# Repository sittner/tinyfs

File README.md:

# TinyFS

TinyFS is a minimalist filesystem designed for extremely constrained embedded systems. The initial reason to create this project was the attempt to build a filesystem that can run on a ZX81 without any additional processors (e.g. an ATMEGA for FAT32 support).

In fact, this was a little bit challenging, because I wanted to use 32k RAM and 32k ROM and due to the architecture of the ZX video system only the lower 16k of ROM is useable for executable code. 8k of that is already used by the original OS, so the code for the FS has to fit into the remaining 8k block. Fortunately the upper 16k is useable to store constant data, so all stuff like that (i.e. strings and initializer data) is stored in that area.

## Quick Start

```c
#include "filesys.h"

int main(void) {
    // Initialize the filesystem
    tfs_init();
    if (tfs_last_error != TFS_ERR_OK) {
        printf("Failed to initialize filesystem\n");
        return 1;
    }
    
    // Write a file
    const char *data = "Hello, TinyFS!";
    tfs_write_file("hello.txt", (uint8_t*)data, strlen(data), 1);
    
    // Read it back
    uint8_t buffer[256];
    uint32_t bytes = tfs_read_file("hello.txt", buffer, sizeof(buffer));
    buffer[bytes] = '\0';
    printf("Read: %s\n", buffer);
    
    return 0;
}
```

See [docs/USAGE_EXAMPLES.md](docs/USAGE_EXAMPLES.md) for more examples.

## Features

TinyFS is designed for extreme simplicity and minimal resource usage, making deliberate trade-offs between features and footprint.

### Capabilities

* **Maximum volume size:** Up to 2TB (terabytes)
* **Maximum file size:** Up to 4GB (gigabytes)
* **Efficient metadata access:** Direct block addressing
* **Low code size:** ~6-15 KB depending on features
* **Low RAM usage:** ~1-3 KB depending on configuration
* **Static memory management:** No dynamic allocation
* **Sequential and random file access:** With Extended API
* **Subdirectory support:** Unlimited nesting depth
* **Portable:** Easy to port to any platform with block storage

### Limitations

To achieve minimal resource usage, the following features are intentionally omitted:

* **No timestamps:** No creation, access, or modification times
* **No file attributes:** No permissions, ownership, or ACLs
* **No caching:** Direct block I/O (simple but slower)
* **No redundancy:** Limited error recovery from corruption
* **Fixed block size:** 512 bytes only (matches SD card sectors)

These trade-offs make TinyFS ideal for extremely constrained systems where FAT32, ext2, or other filesystems won't fit.

## Hardware

The hardware is a ZX81 expansion board consisting of 32kB RAM and ROM as well as
an SD card interface. It was important to me to only use hardware (apart from
the SD card itself) that would also have been available in the era of the ZX81.
That's why I deliberately did not use FPGA, CPLD or coprocessors.

[See the ZXSD schematic](https://github.com/sittner/tinyfs/raw/main/zx81/hardware/zxsd.pdf).

The board contains a memory expansion, because we need some RAM for variables
and buffers and obviously ROM to store the file system code.

The Memory map looks as this:

| Address area    | Mapped device    | Usage                                                          |
|-----------------|------------------|----------------------------------------------------------------|
| 0x0000 - 0x3FFF | ROM (lower 16kB) | 0x0000 - 0x1FFF: Original ROM code (patched with TinyFS hooks) |
|                 |                  | 0x2000 - 0x3FFF: TinyFS code                                   |
| 0x4000 - 0x7FFF | RAM (lower 16kB) | Normal ZX81 RAM (available to the user)                        |
| 0x8000 - 0xBFFF | ROM (upper 16kB) | Constant data for TinyFS                                       |
| 0xC000 - 0xFFFF | RAM (upper 16kB) | 0xC000 - 0xF7FF: Unused (could be used as DFILE e.g. for HRG)  |
|                 |                  | 0xF800 - 0xFFFF: TinyFS variables and buffers                  |

Unfortunately, I've found no easy way to allow RAM in the 0x2000 - 0x3FFF area,
which means that the board will not work with WRX16. The NOP logic of the ZX81
requires that the TinyFS code resides in the lower 32kB area to be executable,
and I've preferred to provide 16kB of RAM.

Other hires systems like WRX1K, Kevin Baker's HIRES16K or HRG-ms seems to work.

Many thanks to Siggi who helped me much in streamlining the memory encoder stuff.

## Supported Platforms

TinyFS has been ported to multiple platforms and can be adapted to any system with block storage.

### Official Ports

* **ZX81** - Z80 with SD card via custom hardware SPI
  - ROM: ~8 KB, RAM: ~1 KB
  - Case-insensitive filenames
  - Sequential access only
  
* **AVR (ATmega328P)** - 8-bit AVR with SD card via hardware SPI
  - Flash: ~10 KB, RAM: ~1 KB
  - Format support
  - Sequential access only
  
* **Linux (FUSE)** - Full-featured desktop implementation
  - File-backed or block device
  - All features enabled
  - Random file access with up to 32 file descriptors

### Custom Platforms

TinyFS can be ported to any platform that provides:
- Block storage with 512-byte sectors (SD/MMC cards, flash, file emulation)
- Approximately 1-3 KB of RAM
- Approximately 6-15 KB of ROM/Flash for code

See [docs/PORTING_GUIDE.md](docs/PORTING_GUIDE.md) for porting instructions.

## Documentation

Comprehensive documentation is available in the `docs/` directory:

* **[ARCHITECTURE.md](docs/ARCHITECTURE.md)** - Filesystem design and internal structures
  - Overview of block types (bitmap, directory, data)
  - Block size and layout details
  - Memory usage and limitations
  
* **[API_REFERENCE.md](docs/API_REFERENCE.md)** - Complete API documentation
  - All public functions with examples
  - Error codes and handling
  - Basic and Extended API reference
  
* **[CONFIGURATION.md](docs/CONFIGURATION.md)** - Configuration options guide
  - Feature flags (format, extended API, etc.)
  - Platform-specific settings
  - Memory vs. features trade-offs
  
* **[USAGE_EXAMPLES.md](docs/USAGE_EXAMPLES.md)** - Practical code examples
  - Basic file operations
  - Directory navigation
  - Random access I/O (Extended API)
  - Error handling patterns
  
* **[PORTING_GUIDE.md](docs/PORTING_GUIDE.md)** - How to port to new platforms
  - Required interface functions
  - Platform examples (AVR, Linux, ZX81)
  - Testing and troubleshooting
  
* **[INTERNAL_DESIGN.md](docs/INTERNAL_DESIGN.md)** - Implementation details
  - Block buffer management
  - Allocation algorithms
  - Seek optimization
  - Performance characteristics

## Ports

### ZX81

All SD card access is done by LOAD and SAVE commands prefixed by a ':' as
file name:

| Command              | Description                                                     |
|----------------------|-----------------------------------------------------------------|
| LOAD ":?"            | show drive info                                                 |
| LOAD ":*"            | show drive info with used blocks (could be very time-consuming) |
| LOAD ":"             | show current dir                                                |
| LOAD ":/"            | change to root dir                                              |
| LOAD ":<"            | change to parent dir                                            |
| LOAD ":>[DIRNAME]"   | change to DIRNAME                                               |
| LOAD ":[FILENAME]"   | load file FILENAME                                              |
| SAVE ":$"            | format disk                                                     |
| SAVE ":>[DIRNAME]"   | create dir DIRNAME                                              |
| SAVE ":=[OLD]:[NEW]" | rename file [OLD] to [NEW]                                      |
| SAVE ":-[FILENAME]"  | delete file [FILENAME]                                          |
| SAVE ":[FILENAME]"   | save file FILENAME                                              |

Without prefix, LOAD/SAVE acts as normal tape operation.

To build the hex file for the ROM you will need [SDCC](https://sdcc.sourceforge.net/)
version [4.5.0](https://sourceforge.net/projects/sdcc/files/sdcc/4.5.0/sdcc-src-4.5.0.tar.bz2/download).

### Linux

To allow easy access to the file system on the SD card from outside the ZX81
world there is a Linux FUSE port as well. This could easily be build via the
included Makefile. As dependency, only libfuse is required.

You can format a SD card, for example:

    sudo ./mktfs /dev/mmcblk0

To mount the SD card, you could use:

    sudo ./tfs -f -o uid=1000,gid=1000,allow_other /dev/mmcblk0 /mnt

Don't forget to umount after work is done:

    sudo umount /mnt

### AVR

This port currently runs on a ATMEGA328P. It provides a simple CLI accessible
via UART @9600 Baud. The main intention of this port was to start developing
the FS code before the actual zx81 hardware was finished, so it is currently
not tested very well.

## Internal structure

Only three types of disk blocks exists:

* Bitmap blocks
* Directory blocks
* Data blocks

### Bitmap blocks

Bitmap blocks are used to track allocated/free blocks. There is stored no meta
data information inside these block, just a plain bit array for 8 x 512 = 4096
bits. If a block is in use, a '1' on the corresponding location is indicating
this.

The bitmap block itself is always marked as used, so the first bit of the bitmap
block is always set to '1'. The following 2023 Blocks can be uses as directory
or data blocks.

Offset calculation is very simple, since the first bitmap block is located on
the beginning of the storage device (block offset 0) and the subsequent bitmap
blocks will be following every 4096 blocks. So the position of the corresponding
bitmap block for a given data/directory block can be calculated by logical
shift/and operations.

The last used bitmap block with free block available is cached in memory to
speed up allocation for data/directory blocks. The bitmap block is needed to read
only once and every following allocation of further blocks just require an write
operation to keep the mapping data on disk up to date. 

### Directory blocks

Directory block are the most complex structures of this file system. They are
used to organize files and subdirectories and store the names of these items.

To allow a virtually unlimited count of items per directory layer and simplify
the process of allocation/freeing directory blocks, they are built as double
linked list. The member *parent* always pointed to the corresponding parent
directory block. A value of '0' is indicating that we are on a root directory
block. The first root directory block on disk could be found on block offset 1.

    typedef struct {
      uint32_t prev;
      uint32_t next;
      uint32_t parent;
      TFS_DIR_ITEM items[];
    } _PACKED TFS_DIR_BLK;

There are 20 items per directory block. An item could be one of the type *free*,
*dir* or *file*. The member *blk* pointed to either the corresponding sub
directory block or to the first data block of the corresponding file. The member
*size* holds the size of the entire file (in case of a subdirectory item it is
set to '0').
    
    #define TFS_NAME_LEN 16

    typedef struct {
      uint32_t blk;
      uint32_t size;
      uint8_t type;
      char name[TFS_NAME_LEN];
    } _PACKED TFS_DIR_ITEM;
    
    #define TFS_DIR_ITEM_FREE 0
    #define TFS_DIR_ITEM_DIR  1
    #define TFS_DIR_ITEM_FILE 2

### Data blocks

These blocks contain the actual file data. They are chained as double linked
list and holding 504 bytes of user data each.

    typedef struct {
      uint32_t prev;
      uint32_t next;
      uint8_t data[];
    } _PACKED TFS_DATA_BLK;

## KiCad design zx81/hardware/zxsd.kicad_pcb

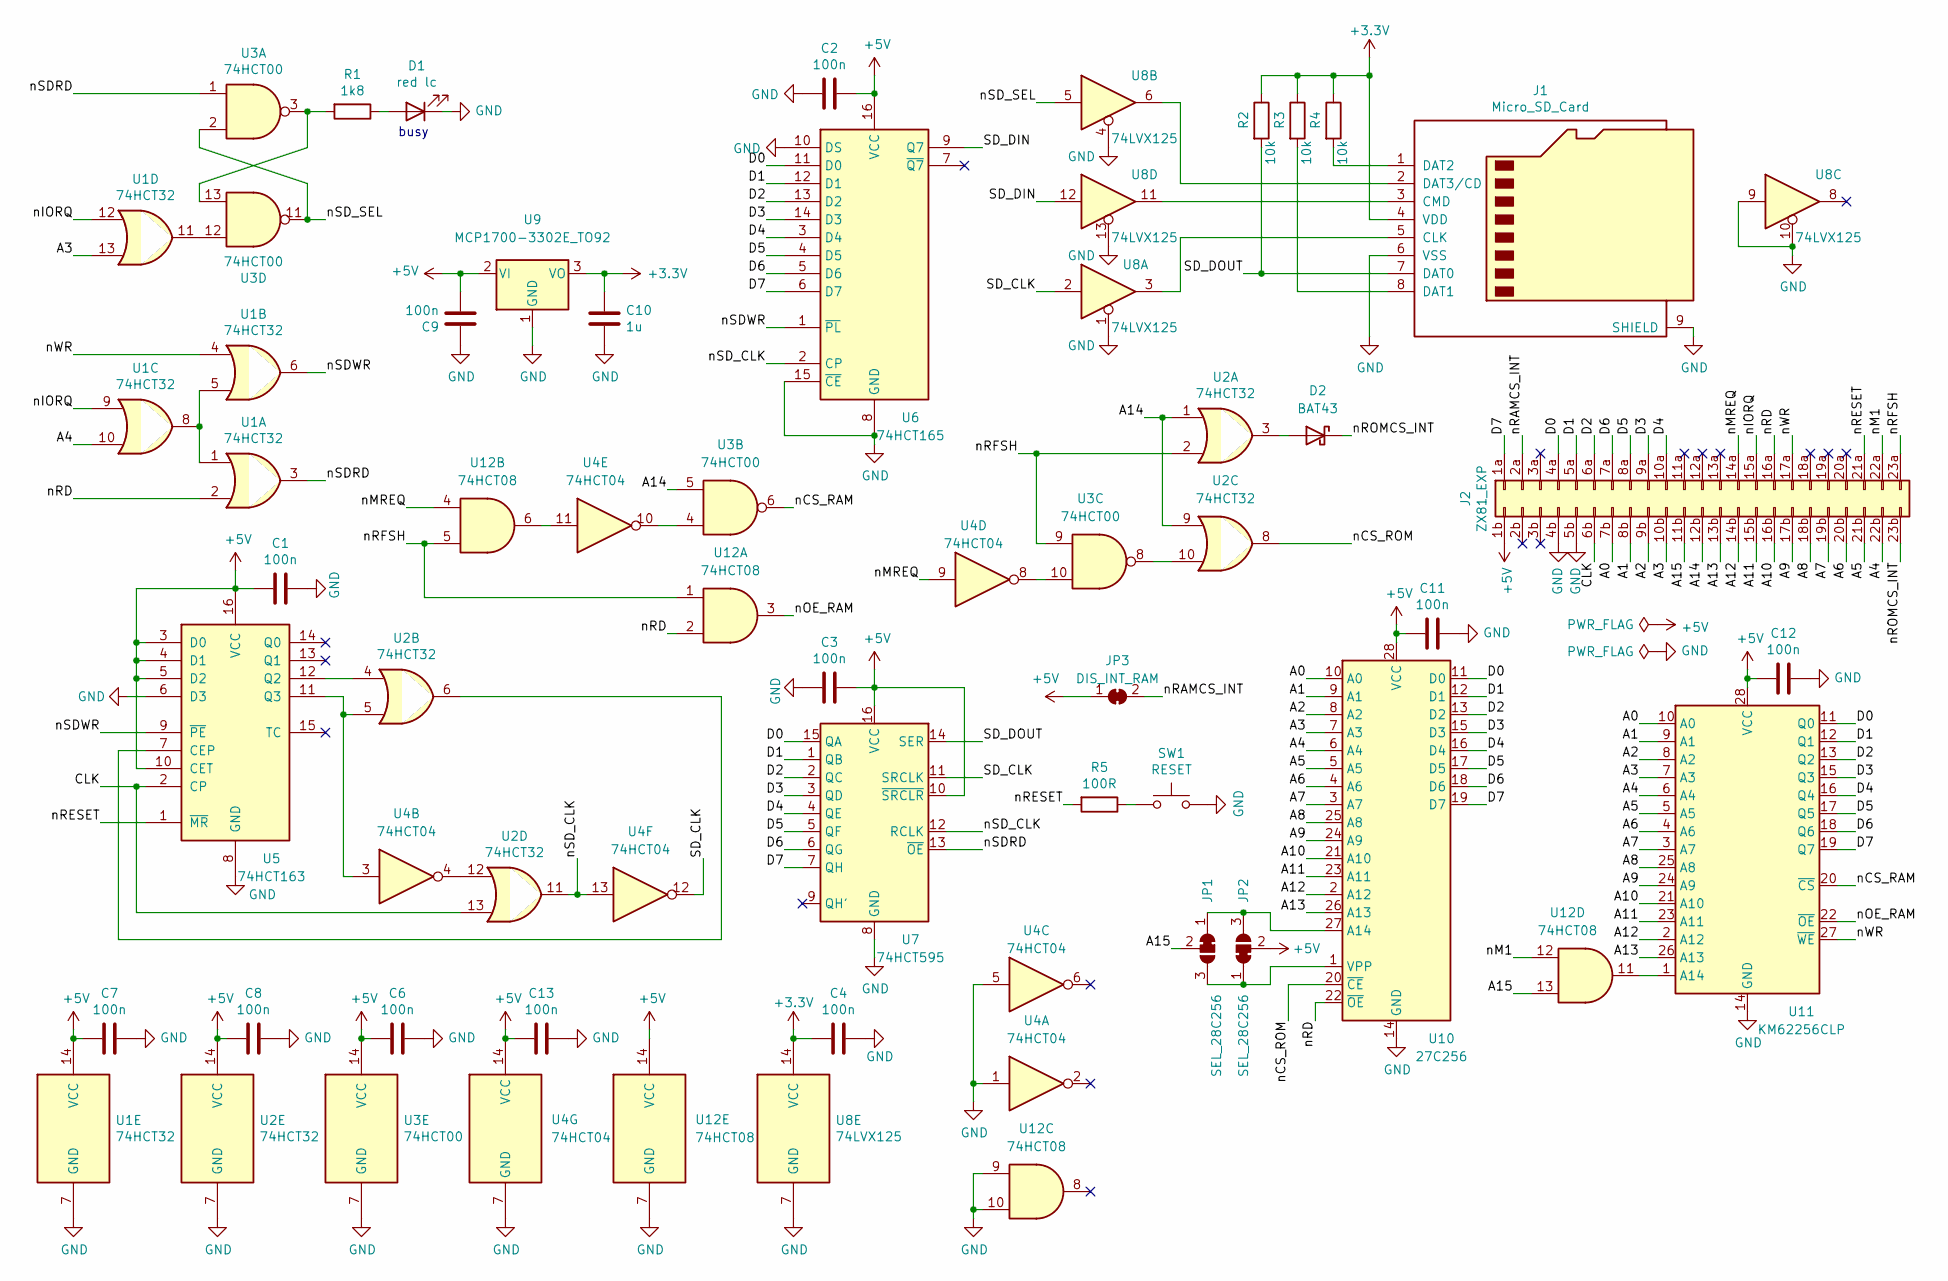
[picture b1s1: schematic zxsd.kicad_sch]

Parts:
C1, C2, C3, C4, C6, C7, C8, C9, C11, C12, C13: 100n; C_Disc_D5.0mm_W2.5mm_P5.00mm
C10: 1u; C_Disc_D5.0mm_W2.5mm_P5.00mm
D1: red lc; LED_D3.0mm
D2: BAT43; D_DO-35_SOD27_P2.54mm_Vertical_AnodeUp
J1: Micro_SD_Card; microSD_HC_Wuerth_693072010801
J2: ZX81_EXP; ZX81_EXP_EXT
JP1, JP2: SEL_28C256; SolderJumper-3_P1.3mm_Bridged12_RoundedPad1.0x1.5mm_NumberL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
JP3: DIS_INT_RAM; SolderJumper-2_P1.3mm_Bridged_RoundedPad1.0x1.5mm
R1: 1k8; R_Axial_DIN0207_L6.3mm_D2.5mm_P10.16mm_Horizontal
R2, R3, R4: 10k; R_Axial_DIN0207_L6.3mm_D2.5mm_P10.16mm_Horizontal
R5: 100R; R_Axial_DIN0207_L6.3mm_D2.5mm_P10.16mm_Horizontal
SW1: RESET; SW_PUSH_6mm
U1, U2: 74HCT32; DIP-14_W7.62mm_Socket_LongPads
U3: 74HCT00; DIP-14_W7.62mm_Socket_LongPads
U4: 74HCT04; DIP-14_W7.62mm_Socket_LongPads
U5: 74HCT163; DIP-16_W7.62mm_Socket_LongPads
U6: 74HCT165; DIP-16_W7.62mm_Socket_LongPads
U7: 74HCT595; DIP-16_W7.62mm_Socket_LongPads
U8: 74LVX125; SO-14_3.9x8.65mm_P1.27mm
U9: MCP1700-3302E_TO92; TO-92_Inline
U10: 27C256; DIP-28_W15.24mm_Socket_LongPads
U11: KM62256CLP; DIP-28_W15.24mm_Socket_LongPads
U12: 74HCT08; DIP-14_W7.62mm_Socket_LongPads

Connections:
+3.3V: C4.2, C10.1, J1.4 (VDD), R2.1, R3.1, R4.1, U8.14 (VCC), U9.3 (VO)
+5V: C1.1, C2.1, C3.1, C6.1, C7.1, C8.1, C9.1, C11.1, C12.1, C13.1, J2.1b, JP2.2 (C), JP3.1 (A), U1.14 (VCC), U2.14 (VCC), U3.14 (VCC), U4.14 (VCC), U5.3 (D0), U5.4 (D1), U5.5 (D2), U5.10 (CET), U5.16 (VCC), U6.16 (VCC), U7.10 (~SRCLR), U7.16 (VCC), U9.2 (VI), U10.28 (VCC), U11.28 (VCC), U12.14 (VCC)
/A0: J2.7b, U10.10 (A0), U11.10 (A0)
/A1: J2.8b, U10.9 (A1), U11.9 (A1)
/A2: J2.9b, U10.8 (A2), U11.8 (A2)
/A3: J2.10b, U1.13, U10.7 (A3), U11.7 (A3)
/A4: J2.22b, U1.10, U10.6 (A4), U11.6 (A4)
/A5: J2.21b, U10.5 (A5), U11.5 (A5)
/A6: J2.20b, U10.4 (A6), U11.4 (A6)
/A7: J2.19b, U10.3 (A7), U11.3 (A7)
/A8: J2.18b, U10.25 (A8), U11.25 (A8)
/A9: J2.17b, U10.24 (A9), U11.24 (A9)
/A10: J2.16b, U10.21 (A10), U11.21 (A10)
/A11: J2.15b, U10.23 (A11), U11.23 (A11)
/A12: J2.14b, U10.2 (A12), U11.2 (A12)
/A13: J2.13b, U10.26 (A13), U11.26 (A13)
/A14: J2.12b, U2.1, U2.9, U3.5
/A15: J2.11b, JP1.2 (C), U12.13
/CLK: J2.6b, U2.13, U5.2 (CP)
/D0: J2.4a, U6.11 (D0), U7.15 (QA), U10.11 (D0), U11.11 (Q0)
/D1: J2.5a, U6.12 (D1), U7.1 (QB), U10.12 (D1), U11.12 (Q1)
/D2: J2.6a, U6.13 (D2), U7.2 (QC), U10.13 (D2), U11.13 (Q2)
/D3: J2.9a, U6.14 (D3), U7.3 (QD), U10.15 (D3), U11.15 (Q3)
/D4: J2.10a, U6.3 (D4), U7.4 (QE), U10.16 (D4), U11.16 (Q4)
/D5: J2.8a, U6.4 (D5), U7.5 (QF), U10.17 (D5), U11.17 (Q5)
/D6: J2.7a, U6.5 (D6), U7.6 (QG), U10.18 (D6), U11.18 (Q6)
/D7: J2.1a, U6.6 (D7), U7.7 (QH), U10.19 (D7), U11.19 (Q7)
/SD_CLK: U4.12, U7.11 (SRCLK), U8.2
/SD_DIN: U6.9 (Q7), U8.12
/SD_DOUT: J1.7 (DAT0), R2.2, U7.14 (SER)
/nCS_RAM: U3.6, U11.20 (~CS)
/nCS_ROM: U2.8, U10.20 (~CE)
/nIORQ: J2.15a, U1.9, U1.12
/nM1: J2.22a, U12.12
/nMREQ: J2.14a, U4.9, U12.4
/nOE_RAM: U11.22 (~OE), U12.3
/nRAMCS_INT: J2.2a, JP3.2 (B)
/nRD: J2.16a, U1.2, U10.22 (~OE), U12.2
/nRESET: J2.21a, R5.2, U5.1 (~MR)
/nRFSH: J2.23a, U2.2, U3.9, U12.1, U12.5
/nROMCS_INT: D2.1 (K), J2.23b
/nSDRD: U1.3, U3.1, U7.13 (~OE)
/nSDWR: U1.6, U5.9 (~PE), U6.1 (~PL)
/nSD_CLK: U2.11, U4.13, U6.2 (CP), U7.12 (RCLK)
/nSD_SEL: U3.2, U3.11, U8.5
/nWR: J2.17a, U1.4, U11.27 (~WE)
GND: C1.2, C2.2, C3.2, C4.1, C6.2, C7.2, C8.2, C9.2, C10.2, C11.2, C12.2, C13.2, D1.1 (K), J1.6 (VSS), J1.9 (SHIELD), J2.4b, J2.5b, SW1.2, U1.7 (GND), U2.7 (GND), U3.7 (GND), U4.1, U4.5, U4.7 (GND), U5.6 (D3), U5.8 (GND), U6.8 (GND), U6.10 (DS), U6.15 (~CE), U7.8 (GND), U8.1, U8.4, U8.7 (GND), U8.9, U8.10, U8.13, U9.1 (GND), U10.14 (GND), U11.14 (GND), U12.7 (GND), U12.9, U12.10
unnamed: D1.2 (A), R1.1
unnamed: D2.2 (A), U2.3
unnamed: J1.1 (DAT2), R4.2
unnamed: J1.2 (DAT3/CD), U8.6
unnamed: J1.3 (CMD), U8.11
unnamed: J1.5 (CLK), U8.3
unnamed: J1.8 (DAT1), R3.2
unnamed: JP1.1 (A), JP2.3 (B), U10.27 (A14)
unnamed: JP1.3 (B), JP2.1 (A), U10.1 (VPP)
unnamed: R1.2, U3.3, U3.13
unnamed: R5.1, SW1.1
unnamed: U1.1, U1.5, U1.8
unnamed: U1.11, U3.12
unnamed: U2.4, U5.12 (Q2)
unnamed: U2.5, U4.3, U5.11 (Q3)
unnamed: U2.6, U5.7 (CEP)
unnamed: U2.10, U3.8
unnamed: U2.12, U4.4
unnamed: U3.4, U4.10
unnamed: U3.10, U4.8
unnamed: U11.1 (A14), U12.11
unnamed: U4.11, U12.6

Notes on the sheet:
busy

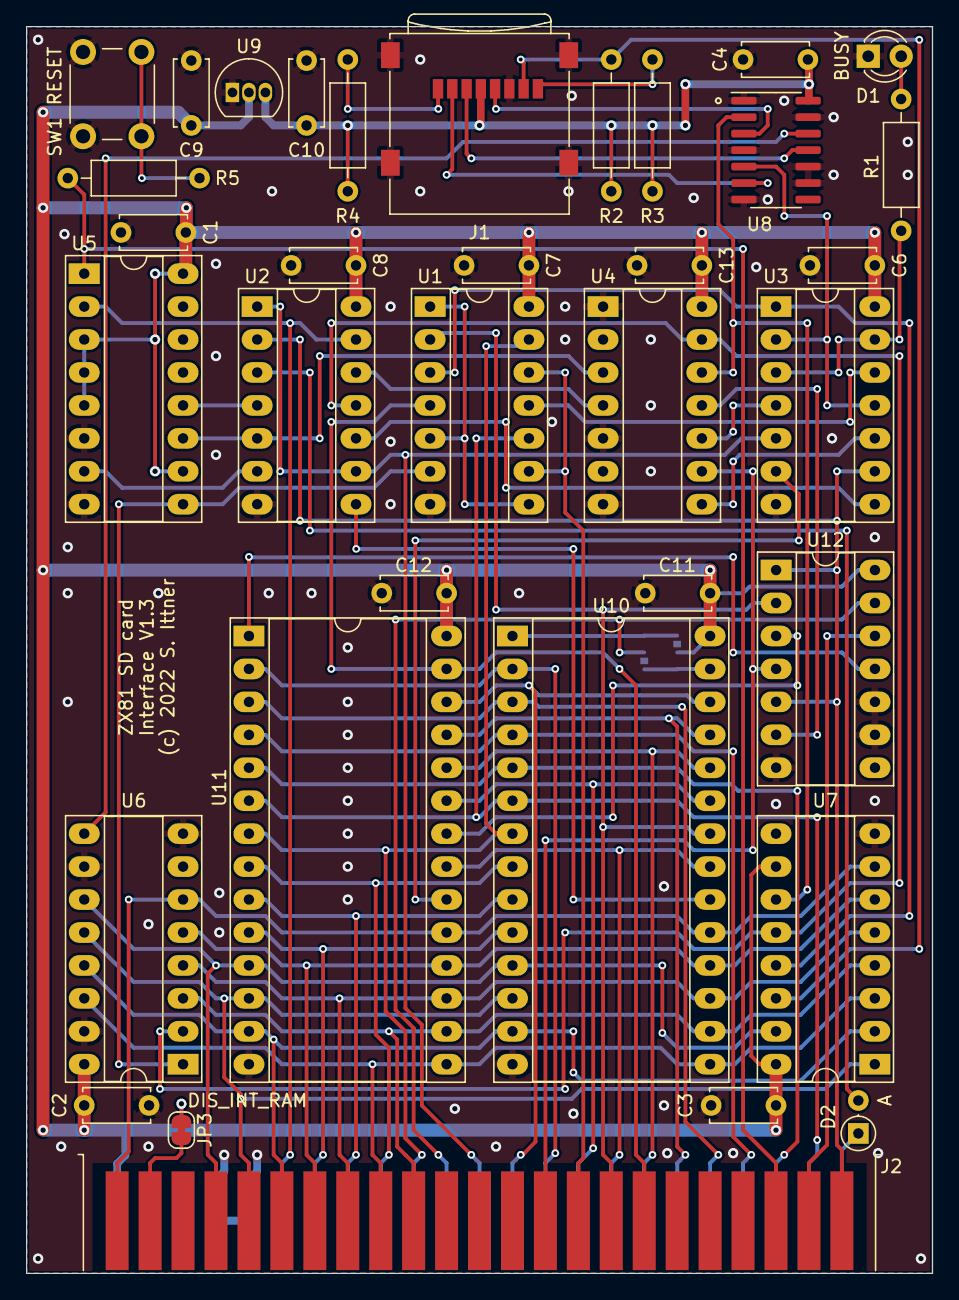
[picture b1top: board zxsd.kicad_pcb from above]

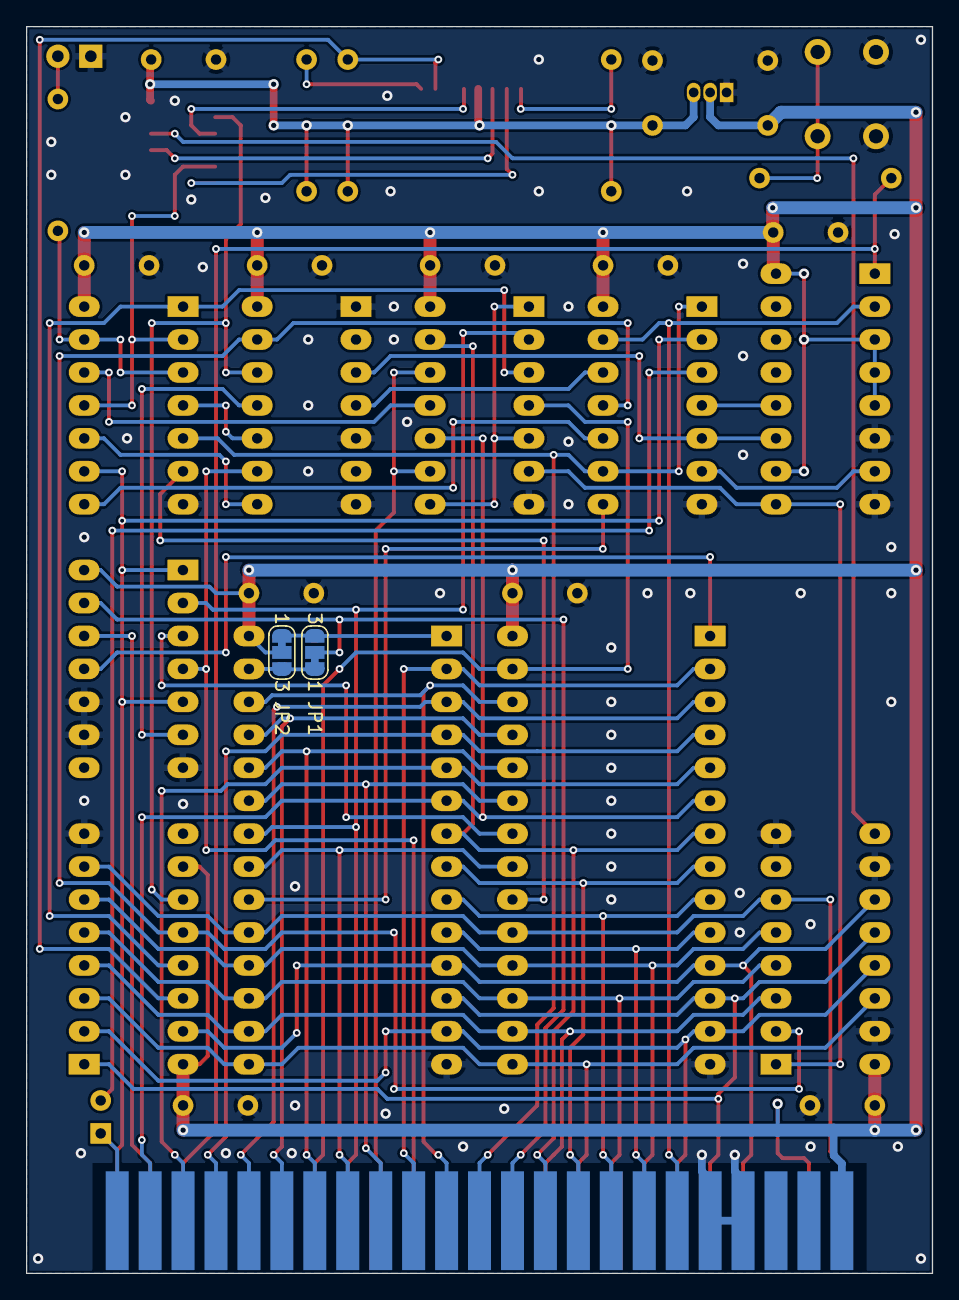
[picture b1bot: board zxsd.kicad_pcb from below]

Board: 2 copper layers, 69.9 x 96.1 mm, 37 parts (2 on the bottom side), 69 nets.

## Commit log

2021-11-28 initial checkin
2021-11-28 clean up bitmap block handling
2021-11-28 clean defines
2021-11-28 fixed parent dir handling
2021-11-28 finished read_file
2021-11-28 implemented delete function
2021-11-28 fixed write_dir_cleanup
2021-11-28 tfs_read_file returns size
2021-11-28 added test commands for file read/write
2021-11-29 fixed last bitmap calulations
2021-11-29 fixed free data block, optimize filename storage
2021-11-29 removed terminal io from filesys.c
2021-11-29 cleanup resetting of last_error
2021-11-29 added support of block device
2021-11-29 removed unused files
2021-11-29 added gitignore file
2021-11-29 named linux port
2021-11-29 implemented static dir entry handler
2021-11-30 - added ports for avr and zx81 - some fixes/cleanups - double chained file blocks - file size up to 4GB
2021-12-02 - finished zx81 file layout - use links for filesys/mmc usage - fixed spi header
2021-12-02 implemented loas/save wrapper functions
2021-12-02 fixed asm code formatting
2021-12-03 fixed slow/fast handling
2021-12-03 fixed format command string
2021-12-03 removed initial switch to FAST mode (we are already there)
2021-12-03 clean up command prefixes
2021-12-03 separate error, if no device found
2021-12-03 added functions to get used blocks and rename files
2021-12-03 moved constant data to 0x8000
2021-12-03 - use of rename/get_used_blocks in main.c - fix to used ascii version of filename
2021-12-03 fixed some warnings
2021-12-04 migrated terminal from absolute positioning to linefeed handling
2021-12-04 renamed CONST segment to CDATA
2021-12-04 clean up term_putc
2021-12-04 moved DATA segment to the end of the upper 16k ram block
2021-12-04 fixed drive select on tfs_get_used
2021-12-04 fixed linux and avr port to match new api
2021-12-04 handle item type on 'show directory' more specific
2021-12-04 optimized mmc.c for code size
2021-12-04 first real spi driver
2021-12-05 fixed filename parameter for load/save function
2021-12-05 added makefile for 16k rom
2021-12-05 fixed dir output format
2021-12-05 fixed handling of dir list abort
2021-12-05 removed one NOP for SPI wait
2021-12-06 fixed 16k rom nameing
2021-12-06 mmc and spi code/performance optimization
2021-12-06 fixed spi optimization
2021-12-06 print drive type as cleartext
2021-12-06 reworked command prefixes
2021-12-06 - trimmed lines in zx81 rom files - term.c uses rom code to clear screen and print char - no switch to slow mode while waiting for key
2021-12-07 report error S on TFS errors
2021-12-07 fixed some ROM symbol names
2021-12-07 removed symbolic links
2021-12-08 use out + value for spi_select_drive/spi_deselect_drive
2021-12-12 added file filesys_priv for fuse support
2021-12-18 implemented linux fuse version
2021-12-18 added range check for linux drive interface
2021-12-18 avr/zx81 fixes for new API
2021-12-18 fixed naming of fuse target
2021-12-18 force single threaded fuse
2021-12-19 optimized seek function
2021-12-19 check filename length
2021-12-19 removed gdb flag
2021-12-19 simplify append logic once more
2021-12-19 better handlig of disk-full condition
2021-12-19 fixed filename length check
2021-12-20 fixed setting of last_error on linux disk interface
2021-12-20 added license file
2021-12-20 added zx81 hardware
2021-12-21 try to speed up tfs_get_used
2021-12-21 fixed error output
2021-12-29 fixed debounce exit state of term_get_key
2021-12-29 fixed error messages
2021-12-29 fixed calculation of last_bitmap_blk/tfs_get_used
2021-12-29 use 74HCT series to be LS/NMOS compatible
2021-12-29 fixed transistor speed boost cap
2021-12-29 fixed .gitignore for kicad
2021-12-29 fixed rom chip select
2021-12-29 updated schematic pdf
2021-12-29 simplified sd card interface
2021-12-29 fixed spi.c for simplified interface
2021-12-29 added function spi_dummy_transfer to support simplified zx81 interface
2021-12-30 cosmetic pcb fixes
2022-01-08 fixed pcb version
2022-01-13 renamed mkfs
2022-01-14 fixed gid value
2022-01-14 fixed parameter handling
2022-01-14 fixed .gitignore
2022-01-15 fixed fd usage_count handling
2022-01-15 added missing file busy check to tfs_write_file
2022-01-19 siplify handling of change directory root/parent
2022-01-19 filename is case insensitive on zx81
2022-01-27 use real jumper for dis_int_ram
2023-01-08 JP4 switches between internal/expansion board RAM
2024-08-30 migrated to KiCAD 6.0
2024-09-09 first draft of documentation finished
2024-09-09 added hardware section
2024-09-09 fixed typo
2024-09-09 use raw links for image/schematic
2024-09-09 fixed gitignore file
2024-09-09 fixed HRG issue, consider nRFSH for memory decoding
2024-09-09 updated pdf schematic
2024-09-12 optimized RAM OE generation (thanks to Sigi)
2024-09-15 some cosmetical fixes
2024-09-15 re-fixed external ROM/EEPROM timing issue
2024-09-16 updated pcb image
2024-09-16 first full decoding for RAM and int+ext ROM
2024-09-16 optimized RAM/ROM decoder logic
2024-09-16 tied ROM CE to GND, only use CE (better timing)
2024-09-19 full decoder logic finished
2024-09-19 re-used ROM's /CE for address decoder, /RD is connected to /OE now
2024-09-19 updated schematic and PCB picture
2024-09-19 hardware description expanded
2024-09-20 added build hint for ZX81 port
2024-09-23 added gerber output directory
2024-10-11 fixed typos
2024-10-11 fixed warnings/syntax issues
2024-10-11 changed calling convention for inline assembler functions
2024-10-11 fixed crt0 for new calling convention
2025-03-20 fixes const flags for string tables
2025-03-20 fixed static for mmc send_command
2025-03-20 fixed last_bitmap_len calculation
2025-03-20 reread diretory block after free data block on file overwrite
2025-08-08 use tfs_ prefix for global last_error and drive_info valiables
2025-08-08 cleanup drive api
2025-08-09 fixed handling of os regs for term_get_key
2025-08-09 updated sdcc version note
2025-08-09 save regs on stack for term_clrscrn and term_putc
2025-12-17 Initial plan
2025-12-17 Add comprehensive TinyFS documentation
2025-12-17 Address code review feedback on documentation
2025-12-17 Correct ZX81 SPI description to custom hardware instead of bit-banged
2025-12-17 Fix critical bugs: file descriptor validation, macro typo, and bounds checking
2025-12-17 Complete critical bug fixes with security analysis
2025-12-17 Fix bounds check to exit both loops when block limit reached
2025-12-17 Use goto instead of variable assignment to save program memory
2025-12-18 updated gitignore file
2025-12-18 Add data response token validation in SD/MMC write operations
2025-12-18 Improve data response token comment clarity

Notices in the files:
zx81/hardware/zxsd.kicad_pcb:
(c) 2022 S. Ittner
